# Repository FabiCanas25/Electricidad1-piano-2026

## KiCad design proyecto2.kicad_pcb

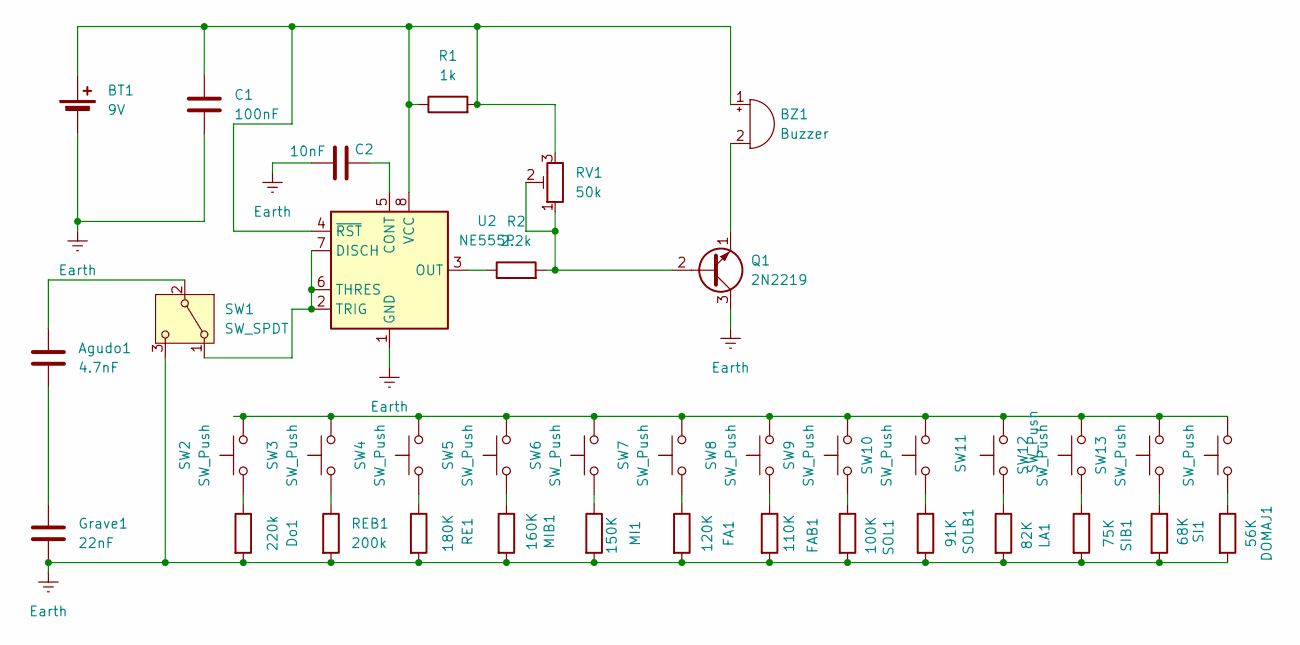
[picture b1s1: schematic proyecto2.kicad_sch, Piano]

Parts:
Agudo1: 4.7nF; CP_Radial_D5.0mm_P2.00mm
BT1: 9V; SolderWire-1.5sqmm_1x02_P7.8mm_D1.7mm_OD3.9mm
BZ1: Buzzer; Buzzer_12x9.5RM7.6
C1: 100nF; CP_Radial_D6.3mm_P2.50mm
C2: 10nF; CP_Radial_D5.0mm_P2.00mm
DOMAJ1: 56K; R_Axial_DIN0207_L6.3mm_D2.5mm_P7.62mm_Horizontal
Do1: 220k; R_Axial_DIN0207_L6.3mm_D2.5mm_P7.62mm_Horizontal
FA1: 120K; R_Axial_DIN0207_L6.3mm_D2.5mm_P7.62mm_Horizontal
FAB1: 110K; R_Axial_DIN0207_L6.3mm_D2.5mm_P7.62mm_Horizontal
Grave1: 22nF; C_Radial_D5.0mm_H11.0mm_P2.00mm
LA1: 82K; R_Axial_DIN0207_L6.3mm_D2.5mm_P7.62mm_Horizontal
MI1: 150K; R_Axial_DIN0207_L6.3mm_D2.5mm_P7.62mm_Horizontal
MIB1: 160K; R_Axial_DIN0207_L6.3mm_D2.5mm_P7.62mm_Horizontal
Q1: 2N2219; TO-39-3
R1: 1k; R_Axial_DIN0207_L6.3mm_D2.5mm_P7.62mm_Horizontal
R2: 2.2k; R_Axial_DIN0207_L6.3mm_D2.5mm_P7.62mm_Horizontal
RE1: 180K; R_Axial_DIN0207_L6.3mm_D2.5mm_P7.62mm_Horizontal
REB1: 200k; R_Axial_DIN0207_L6.3mm_D2.5mm_P7.62mm_Horizontal
RV1: 50k; Potentiometer_Bourns_3296W_Vertical
SI1: 68K; R_Axial_DIN0207_L6.3mm_D2.5mm_P7.62mm_Horizontal
SIB1: 75K; R_Axial_DIN0207_L6.3mm_D2.5mm_P7.62mm_Horizontal
SOL1: 100K; R_Axial_DIN0207_L6.3mm_D2.5mm_P7.62mm_Horizontal
SOLB1: 91K; R_Axial_DIN0207_L6.3mm_D2.5mm_P7.62mm_Horizontal
SW1: SW_SPDT; SW_DIP_SPSTx02_Slide_6.7x6.64mm_W7.62mm_P2.54mm_LowProfile
SW2, SW3, SW4, SW5, SW6, SW7, SW8, SW9, SW10, SW11, SW12, SW13, SW14: SW_Push; SW_PUSH_6mm_H7.3mm
U2: NE555P; DIP-8_W7.62mm

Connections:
Earth: BT1.2 (-), C1.1, C2.1, DOMAJ1.2, Do1.2, FA1.2, FAB1.2, Grave1.2, LA1.2, MI1.2, MIB1.2, Q1.3 (C), RE1.2, REB1.2, SI1.2, SIB1.2, SOL1.2, SOLB1.2, SW1.3 (C), U2.1 (GND)
unnamed: Agudo1.2, Grave1.1
unnamed: BT1.1 (+), BZ1.1 (+), C1.2, R1.1, R1.2, RV1.3, U2.4 (~RST), U2.8 (VCC)
unnamed: BZ1.2 (-), Q1.1 (E)
unnamed: DOMAJ1.1, SW14.1
unnamed: Do1.1, SW2.1
unnamed: FA1.1, SW7.1
unnamed: FAB1.1, SW8.1
unnamed: LA1.1, SW11.1
unnamed: MI1.1, SW6.1
unnamed: MIB1.1, SW5.1
unnamed: Q1.2 (B), R2.2, RV1.1, RV1.2
unnamed: RE1.1, SW4.1
unnamed: REB1.1, SW3.1
unnamed: SI1.1, SW13.1
unnamed: SIB1.1, SW12.1
unnamed: SOL1.1, SW9.1
unnamed: SOLB1.1, SW10.1
unnamed: SW1.1 (A), U2.2 (TRIG), U2.6 (THRES), U2.7 (DISCH)
unnamed: Agudo1.1, SW1.2 (B)
unnamed: SW2.2, SW3.2, SW4.2, SW5.2, SW6.2, SW7.2, SW8.2, SW9.2, SW10.2, SW11.2, SW12.2, SW13.2, SW14.2
unnamed: C2.2, U2.5 (CONT)
unnamed: R2.1, U2.3 (OUT)

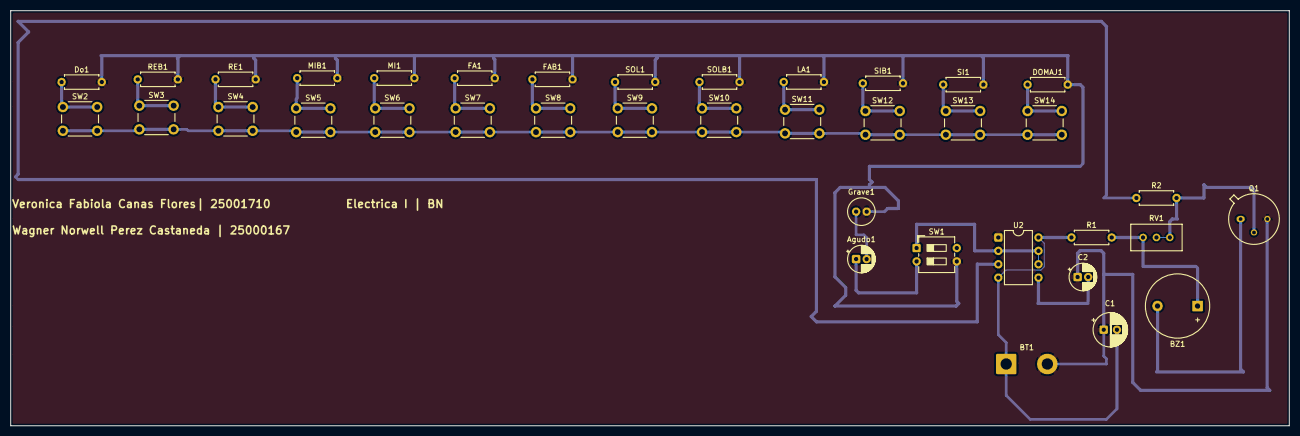
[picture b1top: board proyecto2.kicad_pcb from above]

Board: 2 copper layers, 242.6 x 78.7 mm, 38 parts (0 on the bottom side), 23 nets.
